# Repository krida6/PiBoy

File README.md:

# PiBoy
Development of gameboy based on Raspberry Pi zero W with operation system Retropie.

## Design of PCB
PCB was design in Eagle and all neccassary files can be found in Eagle folder. According the design after the assebley I have discovered that the position of wires is not optimal, because they overlap with speaker in printed case. The PCB must be cut around around ground. The design also contains special board for LCD (need to be cut and will use separately). 

Charging board is not part of design. I have decided to buy charging board for Lithium batteries (approximately 2 dolars) and Boost Step Up converter (approximately 2 dolars). Raspberry Pie can work without step up converter, but you will not use full capacity of battery. The issue is that the battery has voltage from 3.7 to 4.2 V in dependence on state of charge of battery. Optimal voltage for RPI Zero is 5V, but it works from approximately 4 V. I had decided to use step up converter. The capacity of battery was limited by the size of battery. It has to fit into aluminium case with the rest of cirquits. 

Also the switch was connected outside of board and it was glued into front part of case. You need to put the switch on plus (+) of input voltage for RPI Zero.

Moreover left and right  rear buttons are also placed outside board and the are connected with board by thin flexible wires.

If you succesfully solder everything together I can recommend you to cover bottom part of board and raspberry by ducktape (isolation).

Cirquit:

Board:

## Design of case
Everything is placed in aluminium Altoid box. Plastic parts were printed by my friend and it was designed for the project mintyPi. Buttons can be also printed or you can buy them on Aliexpress. Plastic holder parts are glued with aluminum box. Board with Raspberry Pi are joined by screws.

## LCD screen
I have decided for 2.8 inches big lcd screen with resolution 320x240px. We need to remove back board and directly solder the flexible wire on supporting board that is part of designed PCB and need to be cut from PCB.

## Soldering
You need to buy RPi Zero without connector. You have to solder board and RPi Zero together that was the most difficult part. Please use flexible thin wires and do not use long wires. In case of long wires you will not be able to put it together, because limited space in box.

## Finish
If you are lucky you will see something like this.

## Configuration of Retropie
It is strongly recommended to configure static IP adress on device. You can find it here (Setting Static IP):
https://www.instructables.com/Make-Joystic-for-Retropie/

How to configure buttons:
https://learn.adafruit.com/retro-gaming-with-raspberry-pi/adding-controls-hardware?view=all
https://github.com/adafruit/Adafruit-Retrogame
https://learn.adafruit.com/retro-gaming-with-raspberry-pi/configuring-retrogame

How to set LCD:
https://sudomod.com/forum/viewtopic.php?t=2312

Retropie:
https://retropie.org.uk/

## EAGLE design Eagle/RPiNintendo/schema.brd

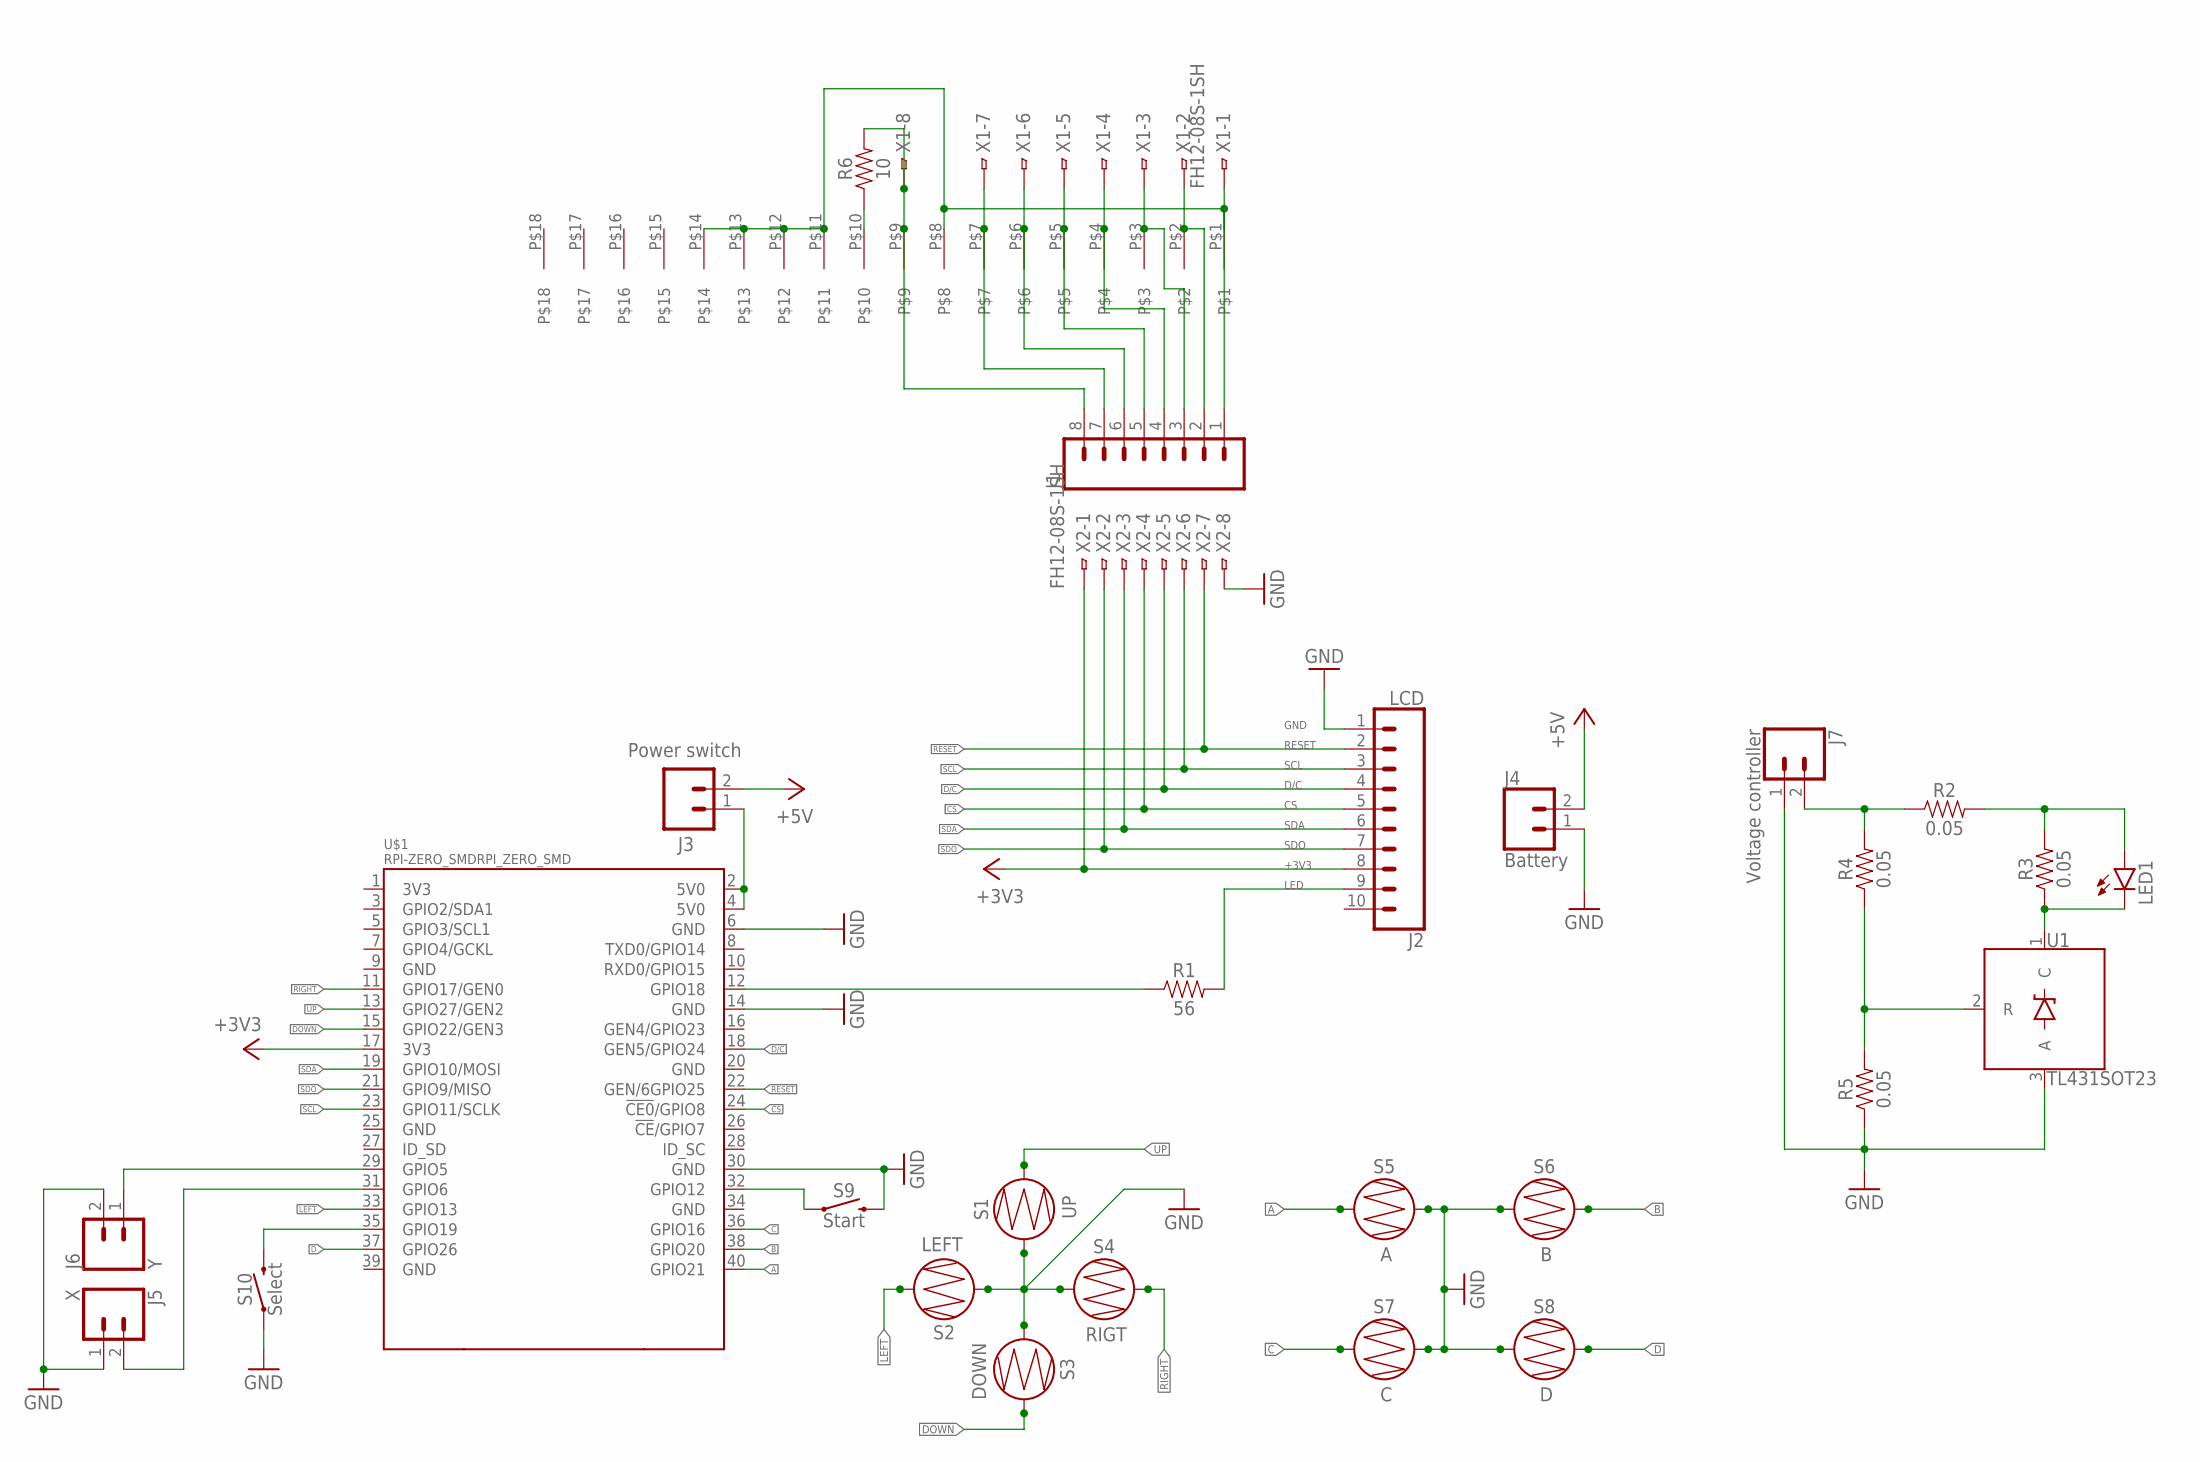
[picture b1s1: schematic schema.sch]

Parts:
J1: CONN_08"; 1X08
J2: LCD; 1X10_NO_SILK
J3: Power switch; 1X02_LOCK_LONGPADS
J4: Battery; 1X02_LOCK_LONGPADS
J5: X; 1X02_LOCK_LONGPADS
J6: Y; 1X02_LOCK_LONGPADS
J7: Voltage controller; 1X02
LED1: LEDKA-3528ASYC; KA-3528ASYC
R1: 56; 0603
R2, R3, R4, R5: 0.05; 0603
R6: 10; 0603
S1: UP; BUTTON-CONDUCTIVE
S2: LEFT; BUTTON-CONDUCTIVE
S3: DOWN; BUTTON-CONDUCTIVE
S4: RIGT; BUTTON-CONDUCTIVE
S5: A; BUTTON-CONDUCTIVE
S6: B; BUTTON-CONDUCTIVE
S7: C; BUTTON-CONDUCTIVE
S8: D; BUTTON-CONDUCTIVE
S9: Start; TACTILE_SWITCH_PTH_6.0MM_KIT
S10: Select; TACTILE_SWITCH_PTH_6.0MM_KIT
U1: TL431SOT23; SOT23-3
U$1: RPI-ZERO_SMDRPI_ZERO_SMD; RASPBERRYPI_SMD
U$2: ILI_LCD
X1, X2: FH12-08S-1SH

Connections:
5V0@2: J3.1, U$1.2 (5V0), U$1.4 (5V0)
+3V3: J2.8, U$1.17 (3V3), X2.1
+5V: J3.2, J4.2
A: S5.1, U$1.40 (GPIO21)
B: S6.2, U$1.38 (GPIO20)
C: S7.1, U$1.36 (GPIO16)
CS: J2.5, U$1.24 (!CE0!/GPIO8), X2.4
D: S8.2, U$1.37 (GPIO26)
D/C: J2.4, U$1.18 (GEN5/GPIO24), X2.5
DOWN: S3.2, U$1.15 (GPIO22/GEN3)
GND: J2.1, J4.1, J5.1, J6.2, J7.1, R5.1, S1.1, S2.1, S3.1, S4.1, S5.2, S6.1, S7.2, S8.1, S9.3 (2), S10.1, U1.3 (A), U$1.6 (GND), U$1.30 (GND), X2.8
GND@4: U$1.14 (GND)
LED: J2.9, R1.2
LEFT: S2.2, U$1.33 (GPIO13)
unnamed: J6.1, U$1.29 (GPIO5)
unnamed: R1.1, U$1.12 (GPIO18)
unnamed: J5.2, U$1.31 (GPIO6)
unnamed: S9.1, U$1.32 (GPIO12)
unnamed: S10.3 (2), U$1.35 (GPIO19)
unnamed: J7.2, R2.1, R4.2
unnamed: LED1.A, R2.2, R3.2
unnamed: LED1.C, R3.1, U1.1 (C)
unnamed: R4.1, R5.2, U1.2 (R)
unnamed: R6.1, U$2.P$10
unnamed: J1.2, U$2.P$2, X1.2
unnamed: J1.3, U$2.P$3, X1.3
unnamed: J1.4, U$2.P$4, X1.4
unnamed: J1.5, U$2.P$5, X1.5
unnamed: J1.6, U$2.P$6, X1.6
unnamed: J1.7, U$2.P$7, X1.7
unnamed: J1.8, R6.2, U$2.P$9, X1.8
unnamed: J1.1, U$2.P$1, U$2.P$8, U$2.P$11, U$2.P$12, U$2.P$13, U$2.P$14, X1.1
RESET: J2.2, U$1.22 (GEN/6GPIO25), X2.7
RIGHT: S4.2, U$1.11 (GPIO17/GEN0)
SCL: J2.3, U$1.23 (GPIO11/SCLK), X2.6
SDA: J2.6, U$1.19 (GPIO10/MOSI), X2.3
SDO: J2.7, U$1.21 (GPIO9/MISO), X2.2
UP: S1.2, U$1.13 (GPIO27/GEN2)

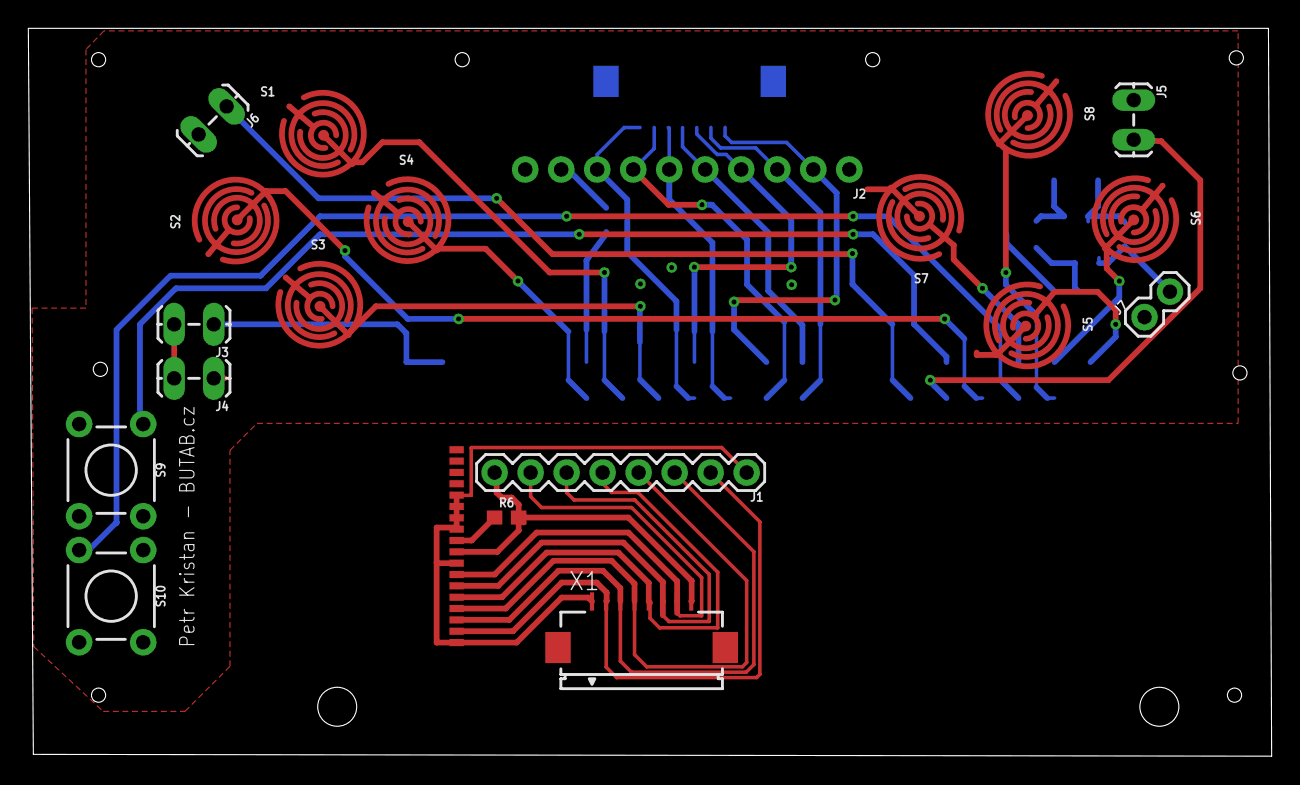
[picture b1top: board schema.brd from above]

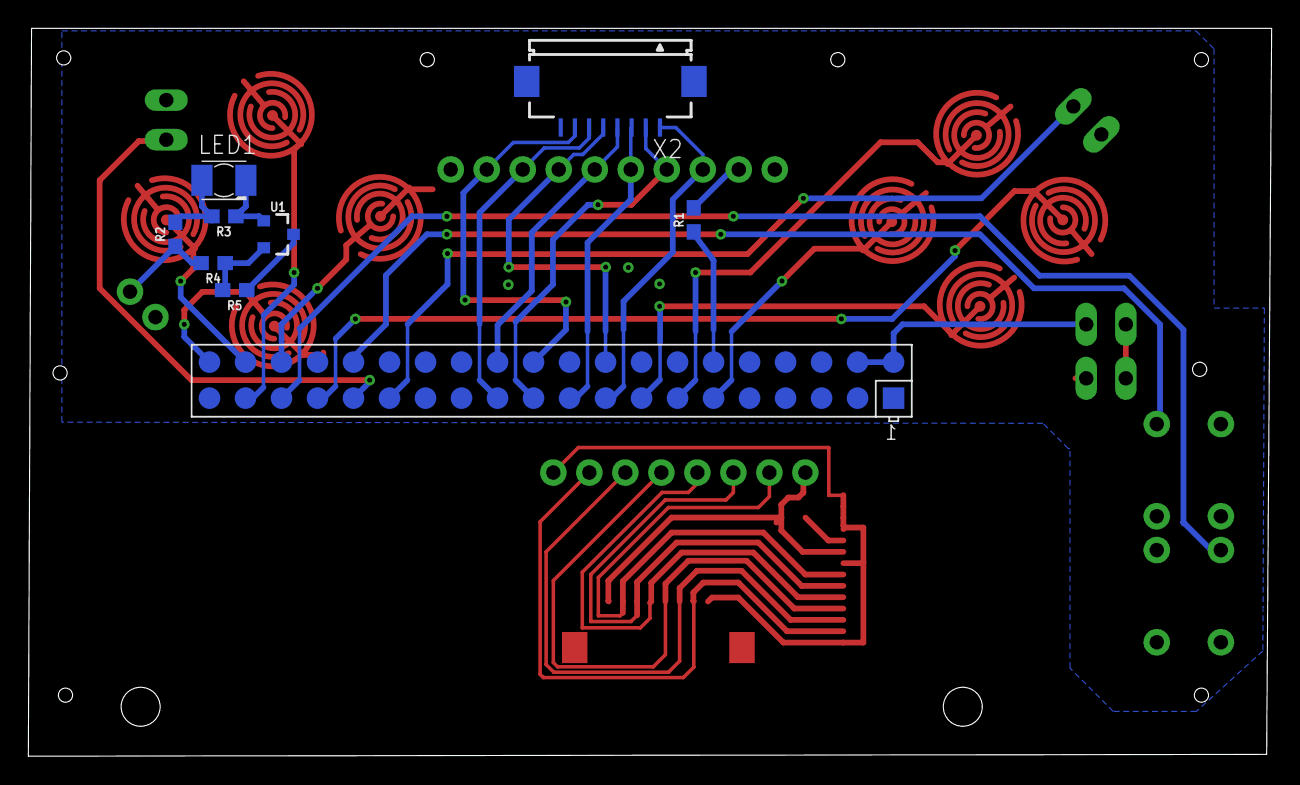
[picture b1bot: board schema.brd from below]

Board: 2 copper layers, 87.7 x 51.3 mm, 29 parts (8 on the bottom side), 37 nets.

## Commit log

2021-01-15 Readme
2021-01-15 correction od readme
2021-01-15 Create README.md
    Corrected readme
2021-02-18 Eagle files for boars, cirquit and libs. More over documentation is also included.
2021-02-18 Images of board and cirquit
2021-02-18 STL files for cover
2021-02-18 STL buttons
2021-02-20 Documentation
2021-02-20 image resize

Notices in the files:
parts and their libraries:
SparkFun-Connectors: Licensing: Creative Commons ShareAlike 4.0 International - https://creativecommons.org/licenses/by-sa/4.0
